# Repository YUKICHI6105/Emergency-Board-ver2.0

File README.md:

# Emergency-Board-ver2.0
Emergency Board ver2.0 2022/10作成

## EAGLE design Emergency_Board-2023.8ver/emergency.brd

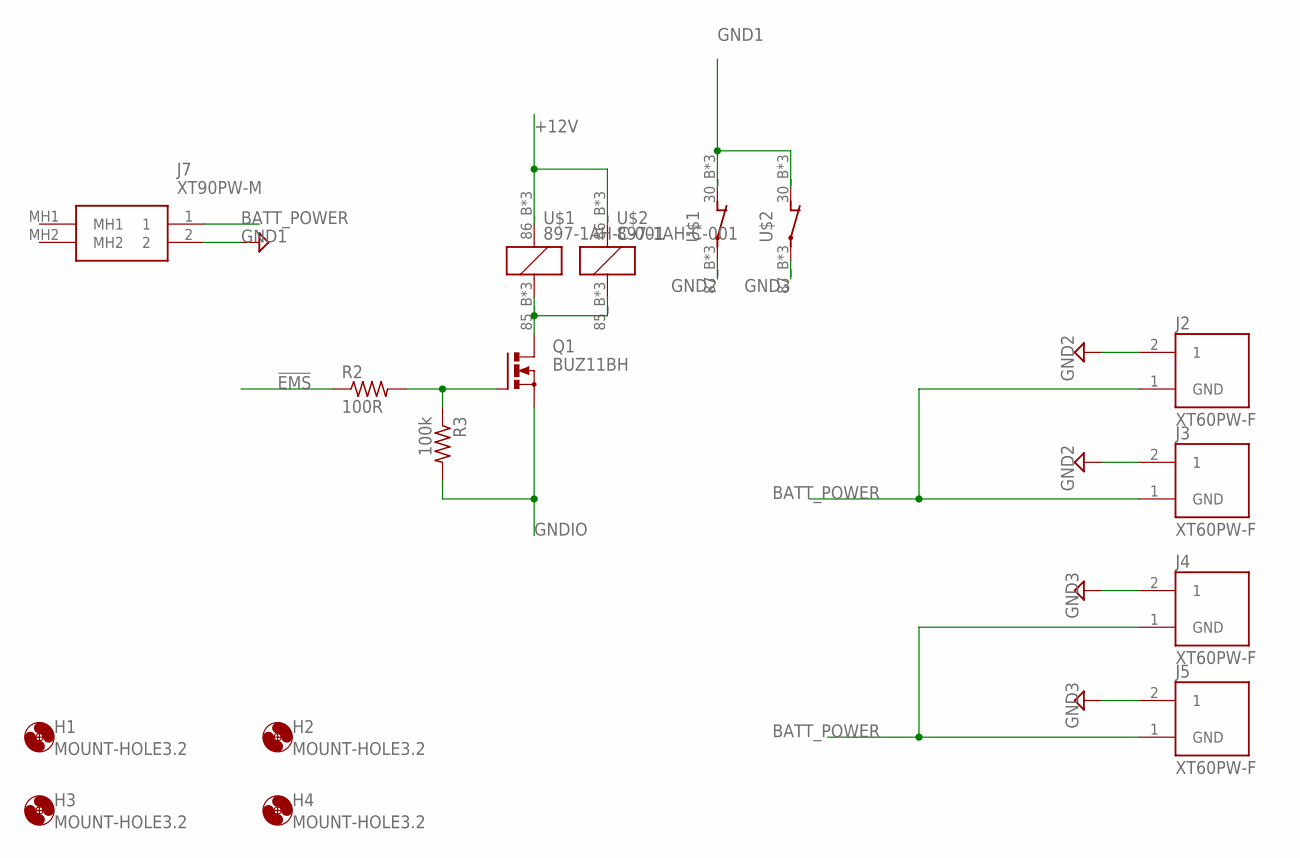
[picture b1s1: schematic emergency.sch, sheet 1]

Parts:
H1, H2, H3, H4: MOUNT-HOLE3.2; 3,2
J2, J3, J4, J5: XT60PW-F; AMASS_XT60PW-F
J7: XT90PW-M; XT90PWM
Q1: BUZ11BH; TO220BH
R2: 100R; R0603
R3: 100k; R0603
U$1, U$2: 897-1AH-C-001

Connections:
!EMS: R2.1; also elsewhere on the board
+12V: U$1.86_B (1), U$1.86_T (1), U$1.P$4 (1), U$2.86_B (1), U$2.86_T (1), U$2.P$4 (1); also elsewhere on the board
BATT_POWER: J2.1 (GND), J3.1 (GND), J4.1 (GND), J5.1 (GND), J7.1
GND1: J7.2, U$1.30_B (O), U$1.30_T (O), U$1.P$3 (O), U$2.30_B (O), U$2.30_T (O), U$2.P$3 (O)
GND2: J2.2 (1), J3.2 (1), U$1.87_B, U$1.87_T, U$1.P$1
GND3: J4.2 (1), J5.2 (1), U$2.87_B, U$2.87_T, U$2.P$1
GNDIO: Q1.S, R3.2; also elsewhere on the board
unnamed: Q1.D, U$1.85_B (2), U$1.85_T (2), U$1.P$2 (2), U$2.85_B (2), U$2.85_T (2), U$2.P$2 (2)
unnamed: Q1.G, R2.2, R3.1

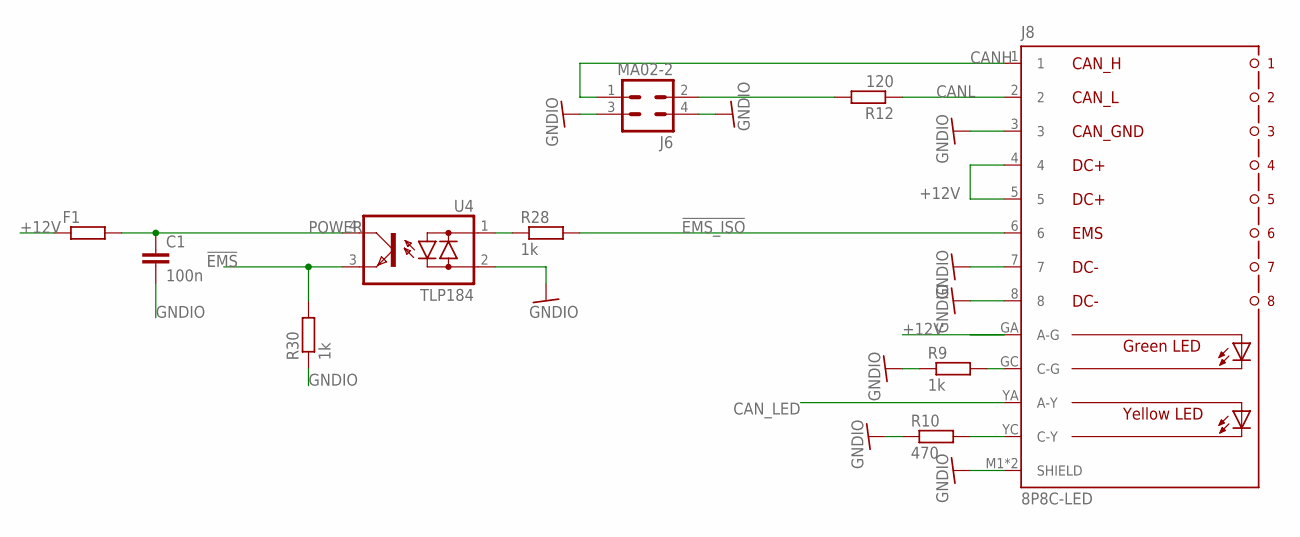
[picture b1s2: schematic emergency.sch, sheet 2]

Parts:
C1: 100n; C0603
F1: R-EU_R1206; R1206
J6: MA02-2; MA02-2W
J8: 8P8C-LED
R9, R28, R30: 1k; R0603
R10: 470; R0603
R12: 120; R0603
U4: TLP184; 11-4M1S

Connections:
!EMS: R30.2, U4.3 (E); also elsewhere on the board
!EMS_ISO: J8.6, R28.2
+12V: F1.1, J8.4, J8.5, J8.GA (A-G); also elsewhere on the board
CANH: J6.1, J8.1
CANL: J8.2, R12.1
CAN_LED: J8.YA (A-Y)
GNDIO: C1.2, J6.3, J6.4, J8.3, J8.7, J8.8, J8.M1 (SHIELD), J8.M2 (SHIELD), R9.1, R10.1, R30.1, U4.2 (AC2); also elsewhere on the board
unnamed: J8.GC (C-G), R9.2
unnamed: J6.2, R12.2
unnamed: J8.YC (C-Y), R10.2
unnamed: R28.1, U4.1 (AC1)
POWER: C1.1, F1.2, U4.4 (C)

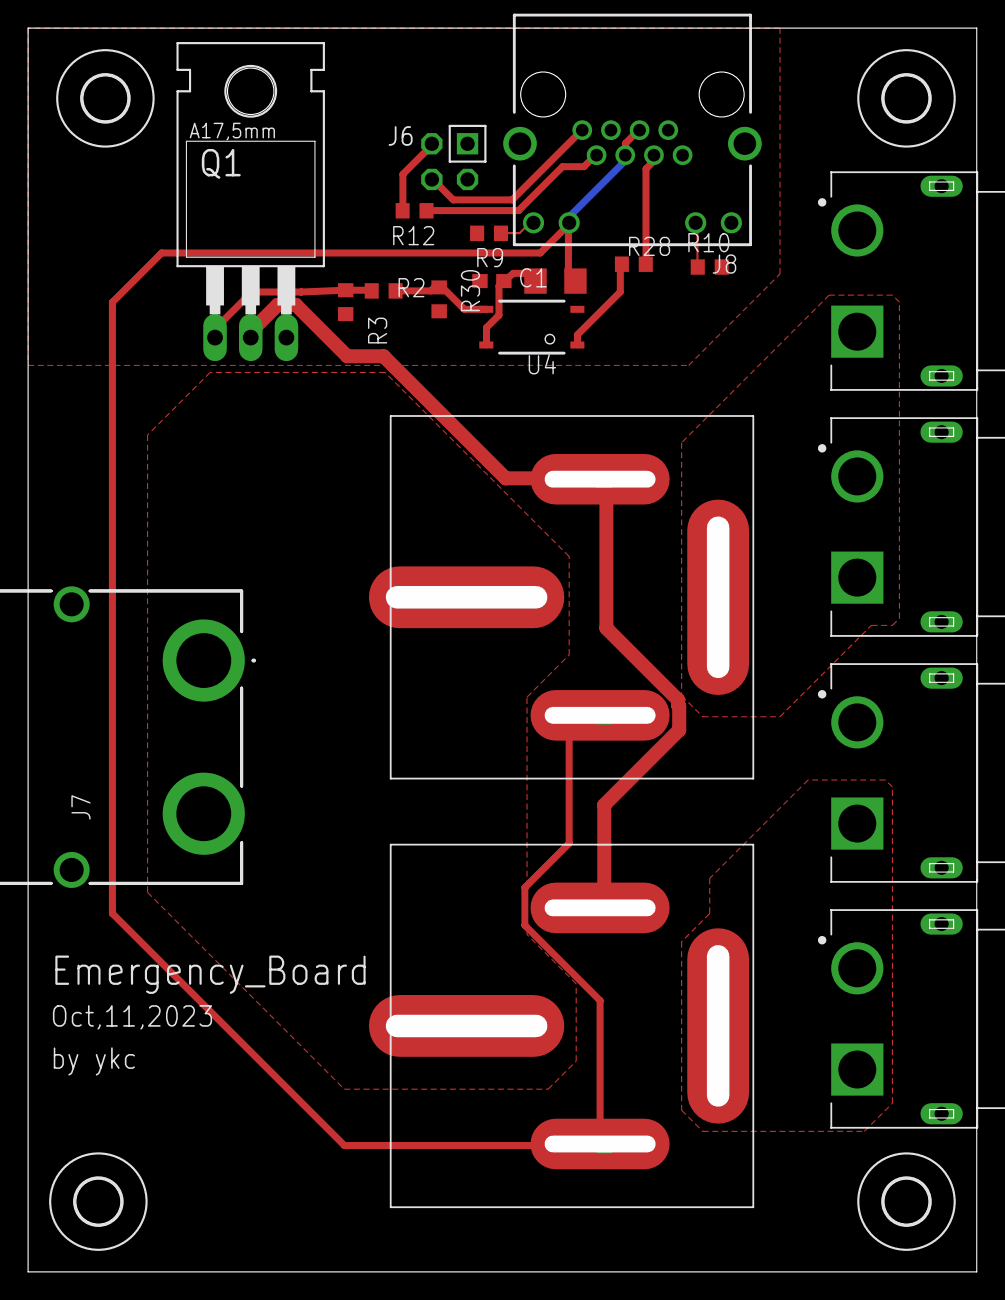
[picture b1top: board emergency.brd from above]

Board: 2 copper layers, 65.9 x 86.9 mm, 24 parts (0 on the bottom side), 17 nets.

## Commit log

2023-08-14 駆動電源を5Vに変更。MOSFETの電流制限抵抗を470(K?)にした方がいいかも
